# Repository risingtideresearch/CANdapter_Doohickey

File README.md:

# CANdapter_Doohickey

Plug the doohickey into the [CANdapter](https://www.ewertenergy.com/products.php?item=candapter) = Get 8P8C x2 + Selectable 120Ohm Termination

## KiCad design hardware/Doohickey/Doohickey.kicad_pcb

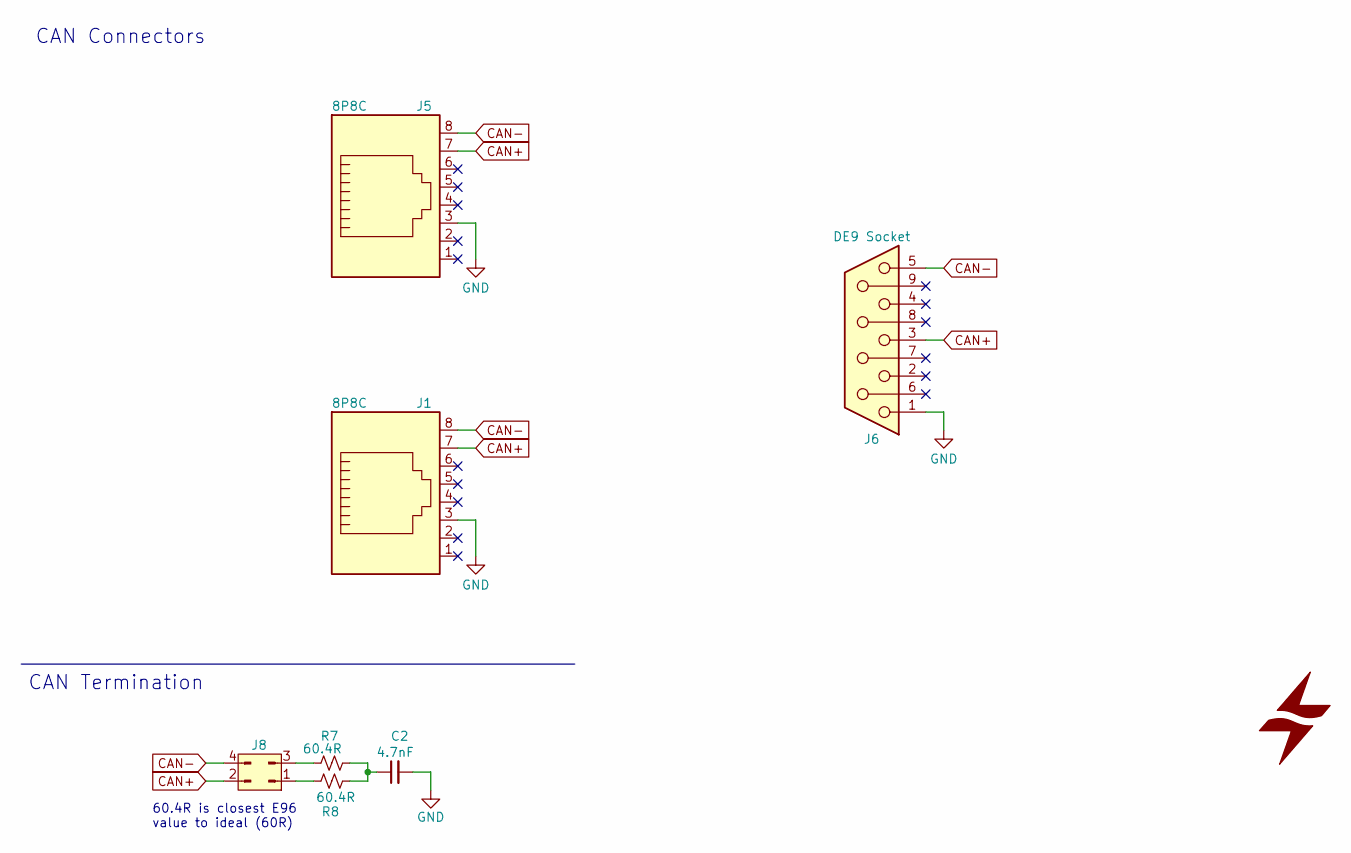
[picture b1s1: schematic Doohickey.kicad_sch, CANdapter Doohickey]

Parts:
C2: 4.7nF; C_0402_1005Metric; Voltage 16V; Tolerance 5%; LCSC C541444
J1, J5: 8P8C; RJ45_Amphenol_RJHSE5380; LCSC C25168869
J6: DE9 Socket; DSUB-9_Pins_Right-Angle
J8: Conn_02x02_Pin; PinHeader_2x02_P2.54mm_Vertical_SMD; LCSC C178293
R7, R8: 60.4R; R_0402_1005Metric; LCSC C60310

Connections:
CAN+: J1.7, J5.7, J6.3, J8.2
CAN-: J1.8, J5.8, J6.5, J8.4
GND: C2.2, J1.3, J5.3, J6.1
unnamed: C2.1, R7.2, R8.1
unnamed: J8.1, R8.2
unnamed: J8.3, R7.1

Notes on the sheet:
CAN Termination
CAN Connectors
60.4R is closest E96 value to ideal (60R)

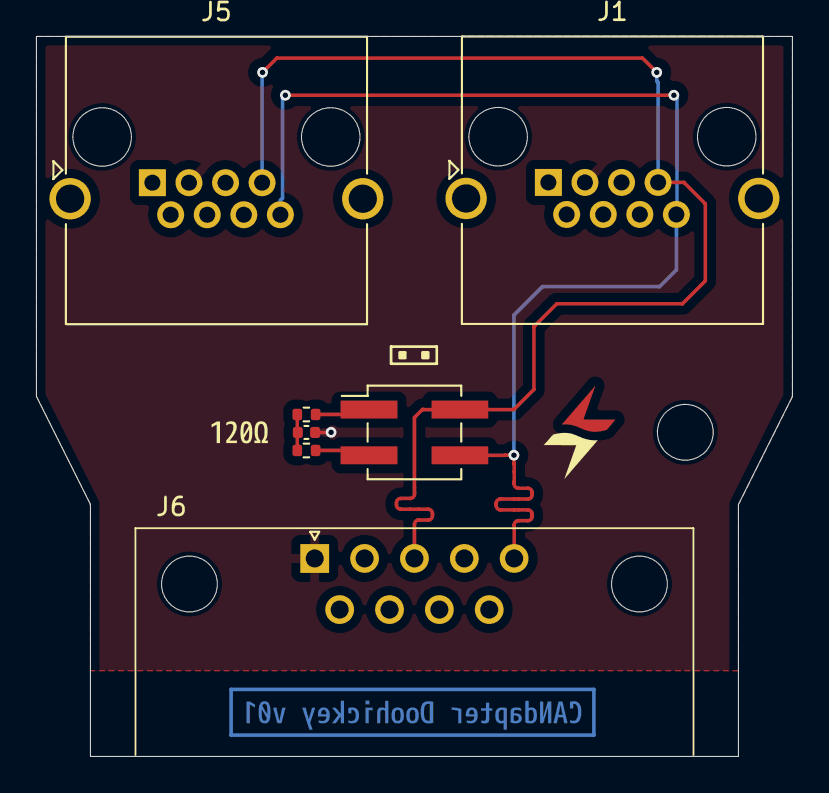
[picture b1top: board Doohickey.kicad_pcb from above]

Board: 2 copper layers, 42.0 x 40.0 mm, 9 parts (1 on the bottom side), 6 nets.

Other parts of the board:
kibuzzard-6AA231C7: G***; kibuzzard-6AA231C7
kibuzzard-6AA23186: G***; kibuzzard-6AA23186
